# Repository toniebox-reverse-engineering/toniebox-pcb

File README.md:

# Toniebox PCB

Repository which will lead to a complete schematic of a Toniebox PCB. The schematic is done with KiCad.

View this project on [CADLAB.io](https://cadlab.io/project/2472). 

Source of CC3200 footprint: https://raw.githubusercontent.com/Turegano/CC3200/master/lib/CC3200.lib

## Table Of Contents
- [Toniebox PCB](#toniebox-pcb)
  - [Table Of Contents](#table-of-contents)
  - [Folders](#folders)
  - [Status](#status)
    - [Remaining Work](#remaining-work)
  - [Block Diagrams](#block-diagrams)
  - [Testpoints](#testpoints)

## Folders

* [datasheets](datasheets/)
* [doc](doc/): documentation
* [library](library/): KiCad libraries

## Status

* red dot: fully documented
* blue dot: partially documented

### Remaining Work

* create subsheets for logical blocks
* create pinout of ASICs
* document remaining testpoints

  T1: NSS40200LTG

## Block Diagrams

## Testpoints

| TP    | Connected to                                                                                                                            | Comment                                                                                                                                                                                                        |
| ----- | --------------------------------------------------------------------------------------------------------------------------------------- | -------------------------------------------------------------------------------------------------------------------------------------------------------------------------------------------------------------- |
| TP1   | U1 MCLK                                                                                                                                 | external master clock                                                                                                                                                                                          |
| TP2   | U1 GPIO1/ U2 pin 55 GPIO1                                                                                                               |                                                                                                                                                                                                                |
| TP3   | K2 pin 9                                                                                                                                | SD detect                                                                                                                                                                                                      |
| TP4   | U2 pin 29                                                                                                                               | ANT SEL1 Antenna Selection Control                                                                                                                                                                             |
| TP5   | U2 pin 30                                                                                                                               | ANT SEL2 Antenna Selection Control                                                                                                                                                                             |
| TP6   | BQ24400 GND/Battery GND                                                                                                                 | Battery GND is connected with PCB GND via R55 (0R05)                                                                                                                                                           |
| TP7   | U2 pin 11/U3 pin 6/R27(?)                                                                                                               | SCK                                                                                                                                                                                                            |
| TP8   | U2 pin 12/U3 pin 5/R26(?)                                                                                                               | SI                                                                                                                                                                                                             |
| TP9   | U2 pin 13/U3 pin 2/R25(?)                                                                                                               | SO                                                                                                                                                                                                             |
| TP10  | U2 pin 14/U3 pin 8/R28(?)                                                                                                               | VCC                                                                                                                                                                                                            |
| TP11  | U7 pin 3 (~LED)                                                                                                                          | Charge status LED, connected to U6 output via 100k pull up and U2 pin 20 via 1k2                                                                                                                               |
| TP12  | U5 ASK/OOK                                                                                                                              | can be configured as an output to provide the received analog signal output                                                                                                                                    |
| TP14  | audio jack                                                                                                                              |                                                                                                                                                                                                                |
| TP15  | audio jack                                                                                                                              |                                                                                                                                                                                                                |
| TP16  | U1 VOL/MICDETECT                                                                                                                        |                                                                                                                                                                                                                |
| TP17  | K9 pin 3/U1                                                                                                                             | speaker+                                                                                                                                                                                                       |
| TP18  | K9 pin 2/U1                                                                                                                             | speaker-                                                                                                                                                                                                       |
| TP19  | U1 pin 31/D12/U2 pin 62 GPIO7/U5 EN                                                                                                     | DAC reset                                                                                                                                                                                                      |
| TP20  | U5 VDD_X                                                                                                                                |                                                                                                                                                                                                                |
| TP21  | U5 VDD                                                                                                                                  |                                                                                                                                                                                                                |
| TP22  | U5 BG                                                                                                                                   |                                                                                                                                                                                                                |
| TP23  | U5 VIN                                                                                                                                  | Voltage of U320, if faulty check TP321                                                                                                                                                                         |
| TP24  | U5 VDD_A                                                                                                                                |                                                                                                                                                                                                                |
| TP25  | U4 pin 3                                                                                                                                | Accelerometer DNC                                                                                                                                                                                              |
| TP26  | K4 pin 1/U2 pin 57/R60 (1k)(?)/R394 (1k2)(?)/                                                                                           | ears, fed from regulator U6/TP52                                                                                                                                                                               |
| TP27  | D10 pin 1                                                                                                                               | LED red -                                                                                                                                                                                                      |
| TP28  | D10 pin 2                                                                                                                               | LED green -                                                                                                                                                                                                    |
| TP29  | D10 pin 3                                                                                                                               | LED blue -                                                                                                                                                                                                     |
| TP30  | U5 IO 5                                                                                                                                 |                                                                                                                                                                                                                |
| TP31  | K4 pin 3/U2 pin 59/R64(1k)(?)                                                                                                           | ears, fed from regulator U6/TP52                                                                                                                                                                               |
| TP32  |                                                                                                                                         |                                                                                                                                                                                                                |
| TP33  | U5 MOD                                                                                                                                  |                                                                                                                                                                                                                |
| TP34  | U5 SYS                                                                                                                                  |                                                                                                                                                                                                                |
| TP35  | U5 EN                                                                                                                                   | When high NFC IC is enabled. If faulty check TP19. Fed by U8 via D13 (is connected to U2 GPIO7).                                                                                                               |
| TP36  | U5 EN2                                                                                                                                  |                                                                                                                                                                                                                |
| TP37  | NFC socket                                                                                                                              |                                                                                                                                                                                                                |
| TP38  | K8 pin 3/T1/D12 (battery control circuit)/T340/T342                                                                                     | bat+                                                                                                                                                                                                           |
| TP39  | U320 VIN, T320 collector voltage for U320 EN via R320; U6 VIN; U8 VIN                                                                   | feeds U320, U6, U8 with VCC; enables U320 via T320                                                                                                                                                             |
| TP41  | Circuit next to U10                                                                                                                     | 0V w/o battery, ~ bat. Voltage w/ battery; output of T344; connected to U10; controls  T343, T342, T340                                                                                                        |
| TP42  | BQ24400 BAT input                                                                                                                       |                                                                                                                                                                                                                |
| TP43  | U10 /                                                                                                                                   | battery voltage after R89; w/ battery: voltage < bat voltage; w/ power supply 3.8 – 4.4V; check TP38 if not ok                                                                                                 |
| TP45  | K8 pin 1/U7 pin 5 (TS)                                                                                                                               | temp sense; connected via R47 with BQ24400 and battery NTC.                                                                                                                                                    |
| TP46  | BQ24400 TIMER PROGRAM                                                                                                                   |                                                                                                                                                                                                                |
| TP47  | U2 pin 8/output L300 via 1:1 voltage divider R75/R72                                                                                    | Supervising U300+circuitry; measured between D301 and L300; 50% voltage via divider R75/R72 to U2 pin 8                                                                                                        |
| TP48  | U2 pin 61/U8 ENABLE via R56 (10k pulldown)                                                                                              | U2 enables LDO U8 with GPIO6. If U8 is not working (TP50) check U8 at TP39                                                                                                                                     |
| TP49  | U2 pin 60                                                                                                                               |                                                                                                                                                                                                                |
| TP50  | U8 VOUT/U9 VIN/U1 IOVDD/U1 HPVDD/SPKVDD/AVDD                                                                                            | 3V3 output of LDO U8, 1V8 input of LDO U9, T11, U4. 3V3 input U1; if not ok check TP48.                                                                                                                        |
| TP51  | U9 VOUT/U1 DVDP                                                                                                                         | 1V8 output of LDO U9. Feeds  U1 at PIN 3; if not ok check ENABLE at TP50 and input voltage at TP39.                                                                                                            |
| TP52  | U6 VOUT 3V3/ U2 VIN IO1, VIN IO2, VIN DCDC ANA, VIN DCDC PA, VIN DCDC DIG, VD2 ANA2/ VCC for U3,T7, T360, T320, SV BQ24400 LED/ RGB LED | 3V3 output LDO U6: feeds U2, U3, T360 (TP360), TP320, LED output of BQ24400 (TP11)                                                                                                                             |
| TP53  | audio jack                                                                                                                              |                                                                                                                                                                                                                |
| TP54  | VCC                                                                                                                                     | Power supply voltage; if power supply is ok check L8 (SMT Common Mode Line Filter 2x500mH)  and D4 (15V TVS Diode)                                                                                             |
| TP55  | GND power jack                                                                                                              |                                                                                                                                                                                                                |
| TP65  | audio jack                                                                                                                              |                                                                                                                                                                                                                |
| TP66  | U2 pin 43/pin 9/pin 56                                                                                                                  | U2 internal voltage                                                                                                                                                                                            |
| TP67  | U2 pin 38/pin 36/pin 48/pin 25                                                                                                          | U2 internal voltage                                                                                                                                                                                            |
| TP68  | U2 pin 48                                                                                                                               | U2 internal voltage                                                                                                                                                                                            |
| TP69  | U2 pin 24                                                                                                                               | U2 internal voltage                                                                                                                                                                                            |
| TP70  | T9                                                                                                                                      | middle pin (SMD 13014)                                                                                                                                                                                         |
| TP71  | U5 VSS PA/VSS RF/VSS/VSS D/NFC connector outer contacts                                                                                 |                                                                                                                                                                                                                |
| TP72  | U1 AIN1                                                                                                                                 |                                                                                                                                                                                                                |
| TP73  | U1 AIN2                                                                                                                                 |                                                                                                                                                                                                                |
| TP74  | U5 IRQ                                                                                                                                  |                                                                                                                                                                                                                |
| TP75  | U300 VIN                                                                                                                                | comes from R305 (0R). U300 generates voltage when operating with power supply; if not ok check TP301                                                                                                           |
| TP300 | U300 ISENS/T347 via R344                                                                                                                | U300 output voltage; main supply when connected to power supply; input voltage of voltage divider R344/R345 for U10.                                                                                           |
| TP301 | D6                                                                                                                                      | Main voltage after D6;if not ok check TP54                                                                                                                                                                     |
| TP320 | U320 ENABLE/T320                                                                                                                        | ENABLE U320 from T320; T320 is supplied via R320 (470k) from D301 (TP39); T320 is controlled by U2 pin 58; if not ok check TP361 and supply voltage of TP39                                                    |
| TP321 | U320 output/U5 input                                                                                                                    | U320 supplies U5; if not ok check TP320 and TP39 for supply voltage; if supply voltage check TP322                                                                                                             |
| TP322 | U320 feedback                                                                                                                           | Voltage for regulating output voltage of U320; output voltage of divider R321 (470k)/R322 (180k); should be 1.31V-1.51V; divider is fed by U320 output; if not ok check output TP321, input TP39, ENABLE TP320 |
| TP341 | U10 circuitry                                                                                                                           | ;output of T347; controls T346, T345, T341;  LOW when operating with power supply; ~ bat voltage when operating with battery; check TP342 and TP38                                                             |
| TP342 | U10 circuitry/voltage divider R344/R345                                                                                                 | Voltage divider R344/R345; fed from output of U300; triggers T344, T347 getriggert; operating with power supply: 1V; battery mode: 0V;check  TP300                                                             |
| TP350 | U2 pin 3                                                                                                                                | I2C_SCL                                                                                                                                                                                                        |
| TP351 | U2 pin 4                                                                                                                                | I2C_SDA                                                                                                                                                                                                        |
| TP355 | config(?) R connected to GND                                                                                                            |                                                                                                                                                                                                                |
| TP356 | config(?) R connected to GND                                                                                                            |                                                                                                                                                                                                                |
| TP357 | config(?) R connected to GND                                                                                                            |                                                                                                                                                                                                                |
| TP358 | config(?) R connected to GND                                                                                                            |                                                                                                                                                                                                                |
| TP360 | K2 pin4                                                                                                                                 | SD VDD;T360 switches  3V3 of U6; T360 is controlled by  U2 GPIO3 PIN58;  check TP361                                                                                                                           |
| TP361 | T320/T360 (voltage)                                                                                                                     | T320 switches ENABLE of U320 / T360 controls voltage SD card                                                                                                                                                   |
| TP370 | U2 pin 34 SOP1                                                                                                                          |                                                                                                                                                                                                                |
| TP371 | U2 pin 35 SOP0                                                                                                                          |                                                                                                                                                                                                                |
| TP372 | U2 pin 17 TDO                                                                                                                           |                                                                                                                                                                                                                |
| TP373 | U2 pin 18                                                                                                                               |                                                                                                                                                                                                                |

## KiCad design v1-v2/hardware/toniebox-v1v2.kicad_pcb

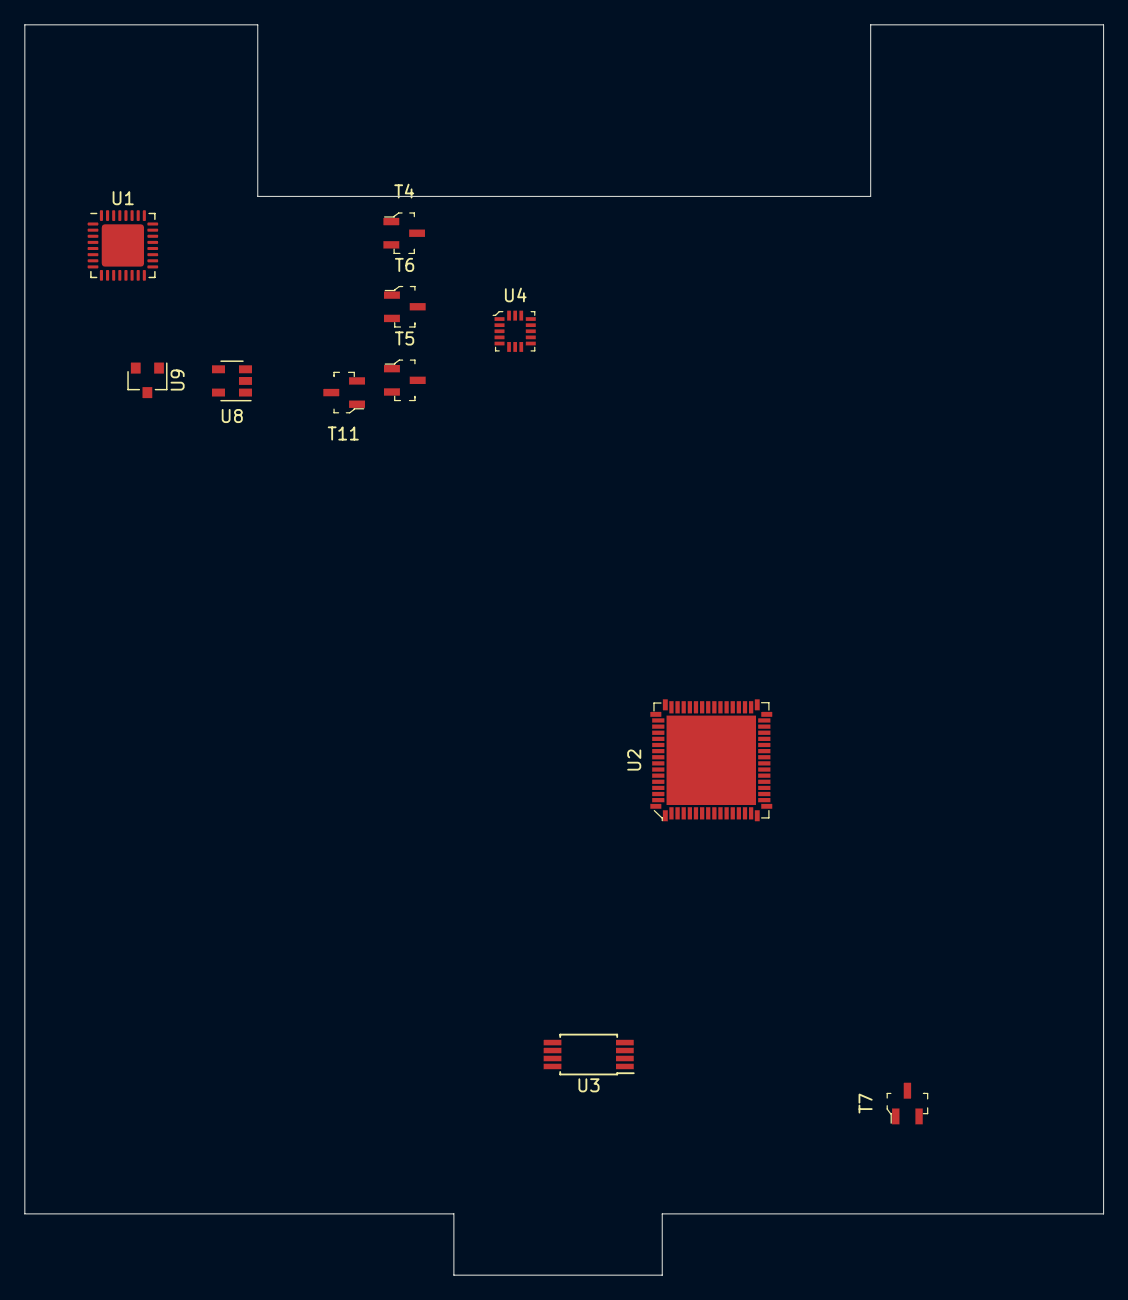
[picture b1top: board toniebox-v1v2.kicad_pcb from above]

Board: 2 copper layers, 88.0 x 102.0 mm, 11 parts (0 on the bottom side), 7 nets, no tracks yet.

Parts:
T4, T5, T6, T7, T11: FDV301N; SOT-23-3
U1: TLV320DAC3100; Texas_S-PVQFN-N32_EP3.45x3.45mm
U2: CC3200R1M2RGCR; VFQFN-64-1EP_9x9mm
U3: IS25LQ032B-JNLE; TSSOP-8_4.4x3mm_P0.65mm
U4: MMA8451QT; VQFN-16_3x3mm
U8: AP2112K-3.3; SOT-23-5
U9: AP2120N-1.8; SOT-23

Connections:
/TBC2: U3.3, U3.7
/TBC3: U2.61, U8.3
GND: T4.2, T5.2, T7.2, T11.2, U1.1
unnamed: T7.1, U2.21
unnamed: T7.3, U2.35
unnamed: T6.2, T11.3
VDD: T11.1, U1.2, U4.1, U8.5

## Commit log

2020-01-20 Deleted README.md
2020-01-20 inital commit
2020-01-20 add cache lib
2020-01-20 add led
2020-01-27 adding testpoints
2020-01-28 LED circuit, more testpoints
2020-01-29 testpoints, LDOs
2020-02-01 add datasheet, progress images, library
2020-02-06 add mosfet datasheet, more ICs
2020-02-10 add fp-* files
2020-02-10 readme
2020-02-11 Backlink to CADLAB.io has been added.
2020-02-20 sd card
2020-02-22 battery, ear connectors;datasheets
2020-05-16 README: more testpoints
2020-10-07 add block diagrams with testpoints
2023-12-08 migrate to kicad 7, add testpoints
2023-12-08 add libraries
2023-12-26 wip: schematic
2024-01-10 add schematic pdf export
